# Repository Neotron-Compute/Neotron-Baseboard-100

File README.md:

# Neotron-Baseboard-100

The Neotron Baseboard 100 is an micro-ATX Neotron motherboard, with Neotron CPU Socket and 4x Neotron Expansion Slots.

You must fit a Neotron CPU card for this board to function (or attach a microcontroller dev-kit of your choice using jumper wires).

### Audio Codec

* Texas Instruments TLV320AIC23B
  * I²S + I²C interface
  * Amplified 32mW headphone output and line out
  * Microphone in and line in
  * TSSOP-28 package
* Triple 3.5mm TRS jack (Kycon STX-4335-5BGP-S1)
  * Headphone Out (green)
  * Line In (blue)
  * Microphone In (pink)
* AC'97 Pin Header
  * Headphone Out
  * Microphone In
* Extra line-level output pin header (e.g. for additional RCA audio jacks - operates in addition to 3.5mm headphone jack output)
* Internal line-level input pin header (e.g. for CD-ROM audio - disabled when line-in 3.5mm jack in-use)

### Super VGA output

* 15-pin D-Sub VGA interface
* 18-bit (6-6-6) RGB R2R DAC
* 3peak TPF133A or Texas Instruments THS7316 RGB video buffer
   * 36 MHz bandwidth - 1024x768@60Hz maximum
   * 6dB gain
   * Drives 75 ohm standard VGA interface
* I²C/DDC level shifter and EMC filter

### RS232 Interface

* Tx, Rx, RTS and CTS signals
* 3.3V TTL on the MCU side
* RS-232 signalling on a 9-pin D-Sub connector (or 10-pin IDC box header), wired DTE

### Board Management Controller

* ST Micro STM32F0 (STM32F030F4P6) microcontroller
  * 32-bit Arm Cortex-M0+ Core
  * 3.3V I/O
  * 8 KiB Flash
  * 4 KiB SRAM
  * TSSOP-20 package
* Controls two PS/2 ports
* Monitors 5V and 3.3V rails
* Controls system reset, soft-on and soft-off for main CPU
* Can the main 5V regulator on and off
* Runs from 3.3V stand-by regulator
* I²C interface (with dedicated IRQ line) with main CPU

| Pin | Name  | Peripheral | Function           |
|:----|:------|:-----------|:-------------------|
| 16  | VDD   | N/A        | 3.3V Digital Power |
| 5   | VDDA  | N/A        | 3.3V Analog Power  |
| 15  | VSS   | N/A        | Ground             |
| 1   | BOOT0 | BOOT0      | Boot Mode Select   |
| 4   | NRST  | Reset      | Reset BMC          |
| 6   | PA0   | ADC0       | Monitor 3.3V rail  |
| 7   | PA1   | ADC0       | Monitor 5V rail    |
| 8   | PA2   | USART1_TX  | Debug Log          |
| 9   | PA3   | Output     | Status LED         |
| 10  | PA4   | Output     | DC-DC Enable       |
| 11  | PA5   | Output     | System Reset       |
| 12  | PA6   | Input      | Reset Switch In    |
| 13  | PA7   | Input      | Power Switch In    |
| 17  | PA9   | I2C0_SCL   | Host comms         |
| 18  | PA10  | I2C0_SDA   | Host comms         |
| 19  | PA13  | IO         | PS/2 Data 1        |
| 20  | PA14  | IO         | PS/2 Clock 1       |
| 14  | PB1   | Output     | Host IRQ           |
| 2   | PF0   | IO         | PS/2 Data 0        |
| 3   | PF1   | IO         | PS/2 Clock 0       |

### PS/2 Keyboard and Mouse

* Twin mini 6-pin DIN ports
* Controlled via Board Management Controller

### Power Supply

* Unregulated 12V (8V to 28V) input fused with a PTC at 2A
* 3A 5.0V main regulator (DC-DC switch-mode regulator module)
* 30mA 3.3V stand-by regulator (a micropower linear regulator)
* 1A 3.3V regulator (a high-power 1117 type linear regulator)
* Controlled by the Board Management Controller

### CPU Socket

The CPU can either be designed to solder direct to your particular motherboard design, or it can be fitted to a second PCB 'CPU card' which plugs into a socket on the motherboard. We have designed a special 80-pin socket pinout, which provides all the signals for required for the standard peripherals available in this design.

The socket is basically two 2x20 pin headers, placed 130 mil apart. This should give enough space to fit even a TQFP-176 microcontroller and some TSOP-54 SDRAM.

The pins are labelled in row.column fashion, i.e. 1.1 is top left, 1.20 is top right and 4.20 is bottom right.

```
 +----- Pin 1.1
 |
 v
+---------------------------------------+
|o o o o o o o o o o o o o o o o o o o o|
|o o o o o o o o o o o o o o o o o o o o|
+---------------------------------------+

+---------------------------------------+
|o o o o o o o o o o o o o o o o o o o o|
|o o o o o o o o o o o o o o o o o o o o|
+---------------------------------------+
                                       ^
                                       |
                         Pin 4.20 -----+
```

| Pin  | Function             |
|:-----|:---------------------|
| 1.1  | VGA_RED5             |
| 1.2  | VGA_RED4             |
| 1.3  | VGA_RED3             |
| 1.4  | VGA_RED2             |
| 1.5  | VGA_RED1             |
| 1.6  | VGA_RED0             |
| 1.7  | VGA_GREEN5           |
| 1.8  | VGA_GREEN4           |
| 1.9  | VGA_GREEN3           |
| 1.10 | VGA_GREEN2           |
| 1.11 | VGA_GREEN1           |
| 1.12 | VGA_GREEN0           |
| 1.13 | VGA_BLUE5            |
| 1.14 | VGA_BLUE4            |
| 1.15 | VGA_BLUE3            |
| 1.16 | VGA_BLUE2            |
| 1.17 | VGA_BLUE1            |
| 1.18 | VGA_BLUE0            |
| 1.19 | VGA_HSYNC            |
| 1.20 | VGA_VSYNC            |
| 2.1  | VGA_DDC_SDA          |
| 2.2  | VGA_DDC_SCL          |
| 2.3  | UART_RX              |
| 2.4  | UART_TX              |
| 2.7  | 3V3                  |
| 2.8  | 3V3                  |
| 2.9  | 3V3                  |
| 2.10 | GND                  |
| 2.11 | GND                  |
| 2.12 | GND                  |
| 2.13 | AUDIO_BCLK_TO_CODEC  |
| 2.14 | AUDIO_DAT_TO_CODEC   |
| 2.15 | AUDIO_LR_TO_CODEC    |
| 2.16 | AUDIO_DAT_FROM_CODEC |
| 2.17 | AUDIO_LR_FROM_CODEC  |
| 2.18 | USB_EN               |
| 2.19 | USB_D-               |
| 2.20 | USB_D+               |
| 3.1  | I2C_SDA              |
| 3.2  | I2C_SCL              |
| 3.3  | UART_CTS             |
| 3.4  | UART_RTS             |
| 3.7  | GND                  |
| 3.8  | GND                  |
| 3.9  | GND                  |
| 3.10 | 5V                   |
| 3.11 | 5V                   |
| 3.12 | 5V                   |
| 3.13 | ~SPI_CS7             |
| 3.14 | ~SPI_CS6             |
| 3.15 | ~SPI_CS5             |
| 3.16 | ~SPI_CS4             |
| 3.17 | ~SPI_CS3             |
| 3.18 | ~SPI_CS2             |
| 3.19 | ~SPI_CS1             |
| 3.20 | ~SPI_CS0             |
| 4.1  | ~SDMMC_CARD_DETECT   |
| 4.2  | ~SDMMC_WRITE_PROT    |
| 4.3  | SDMMC_DAT2           |
| 4.4  | SDMMC_DAT3           |
| 4.5  | SDMMC_CMD            |
| 4.6  | SDMMC_CLK            |
| 4.7  | SDMMC_DAT0           |
| 4.8  | SDMMC_DAT1           |
| 4.9  | SPI_COPI             |
| 4.10 | SPI_CIPO             |
| 4.11 | SPI_CLK              |
| 4.12 | ~RESET               |
| 4.13 | ~IRQ7                |
| 4.14 | ~IRQ6                |
| 4.15 | ~IRQ5                |
| 4.16 | ~IRQ4                |
| 4.17 | ~IRQ3                |
| 4.18 | ~IRQ2                |
| 4.19 | ~IRQ1                |
| 4.20 | ~IRQ0                |

## Expansion

The (up-to) seven expansion sockets allow you to add on I²C or SPI based devices at a later date. Each provides a single chip-select and a single IRQ line - the motherboard design should ensure each socket gets a unique signal for each of these. Each expansion device should also contain a AT24C256 or similar EEPROM device. To allow these EEPROM devices to be scanned, each slot also contains three `EEPROM_ADDRESS` pins, tied to Vcc or GND in a unique combination. These should be connected through to the EEPROM address lines on your AT24C256, thus ensuring that each expansion card has its EEPROM at a unique address - 0x50 on Slot 0 through to a maximum possible 0x57 for Slot 7. Where your board has on-board devices, you should fit an AT24C256 EEPROM for each device so that the on-board devices can be discovered, exactly as if they were on an expansion card.

The expansion slot is a simple 2x10 header. We suggest the use of a TE card-edge connector, but you could equally use two 1x10 pin-headers if desired.

The pin functions are:

```
     SPI_COPI   1    2   GND
     SPI_CIPO   3    4   GND
      SPI_CLK   5    6   GND
      ~SPI_CS   7    8   ~IRQ
      I2C_SDA   9   10   I2C_SCL
 EEPROM_ADDR0   11  12   EEPROM_ADDR1
 EEPROM_ADDR2   13  14   ~RESET
           5V   15  16   5V
          3V3   17  18   3V3
          GND   19  20   GND
```

## Expansion Ideas

Why not design and build your own expansion card? You could try designing:

* A dual Atari/SEGA 9-pin Joypad Interface
* An Ethernet card, e.g. with an ENC28J60 SPI/Ethernet interface IC
* A Mikro Eletronika Click adaptor, allow many of the range of [Click board](https://www.mikroe.com/click) to be fitted
* A Wi-Fi/Bluetooth card, using an Espressif ESP32
* A second processor card - perhaps with a RISC-V microcontroller, or classic Zilog Z80
* An OPL2 or OPL3 based FM synthesiser card
* An ISA adaptor card (taking an ISA card at right-angles, i.e. parallel to the base board) - a simple microcontroller should be able to bit-bang the ISA bus at 8 MHz and offer an SPI peripheral interface to the Neotron Expansion Slot
* An IDE interface card, allowing 40-pin IDE Hard Disk Drives and CD-ROM drives to be used - this will be quite similar to an ISA bus adaptor
* A floppy drive controller card - either using an eSPI Super I/O chip, or connecting a legacy ISA bus floppy controller as per the ISA adaptor
* A video card for a second monitor output, perhaps based on the CPLD used in the [VGAtonic](https://hackaday.io/project/6309-vga-graphics-over-spi-and-serial-vgatonic)

## Changelog

See [CHANGELOG.md](./CHANGELOG.md) for a list of detailed changes.

## Licence

This schematic and PCB design is Copyright (c) The Neotron Developers.

This work is licensed under a [Creative Commons Attribution-ShareAlike 4.0 International License](http://creativecommons.org/licenses/by-sa/4.0/).

## Contribution Agreement

Unless you explicitly state otherwise, any contribution intentionally submitted for inclusion in the work by you, as defined in the Apache-2.0 license, shall be licensed as above, without any additional terms or conditions.

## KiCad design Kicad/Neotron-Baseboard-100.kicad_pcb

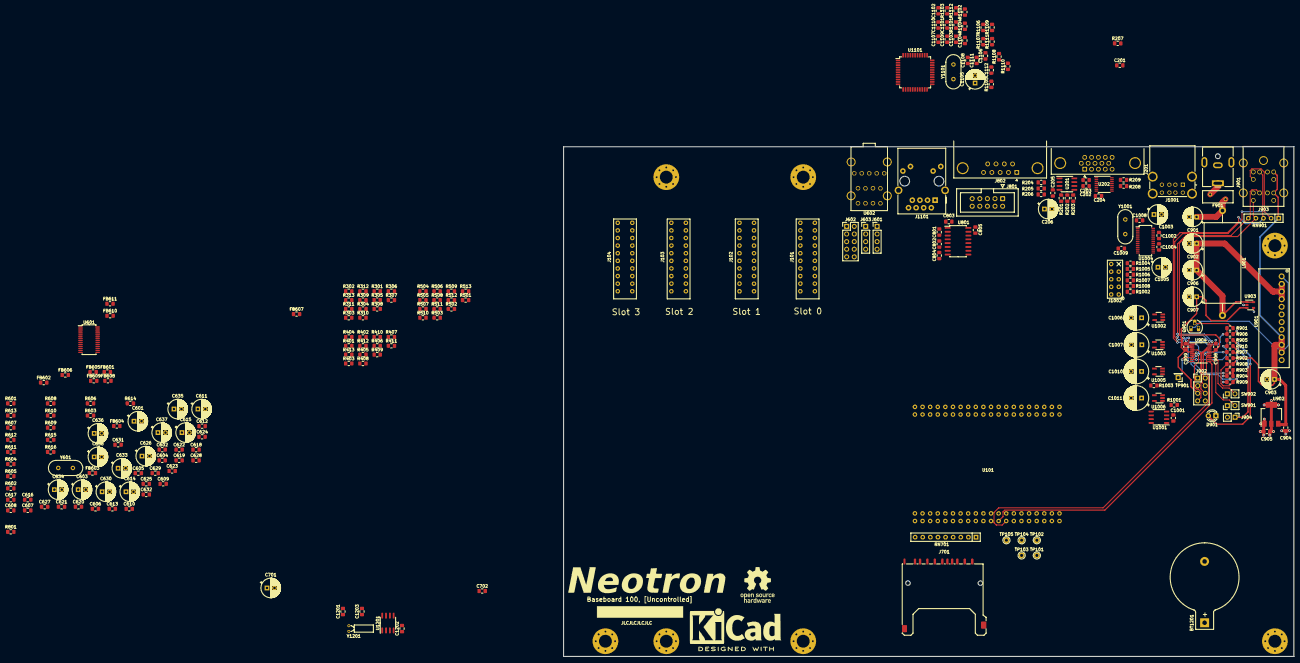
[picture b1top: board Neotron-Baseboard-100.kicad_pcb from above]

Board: 4 copper layers, 243.8 x 170.2 mm, 257 parts (0 on the bottom side), 218 nets.

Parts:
BT1201: Coin Cell; BatteryHolder_Keystone_103_1x20mm
C201: 220n; C_0805_2012Metric_Pad1.15x1.40mm_HandSolder
C202, C203, C204, C205, C602, C604, C612, C613, C627, C702, C801, C802, C803, C804, C805, C904, C908, C909, C1001, C1002, C1004, C1106, C1107, C1108, C1109, C1110, C1201: 100n; C_0805_2012Metric_Pad1.15x1.40mm_HandSolder
C206, C601, C603, C611, C626, C633, C634, C635, C636, C637, C638, C701: 10u; CP_Radial_D6.3mm_P2.50mm
C605, C606, C620, C621: 470n; C_0805_2012Metric_Pad1.15x1.40mm_HandSolder
C607, C608, C609, C610, C616, C617, C618, C619, C622, C623, C624, C625, C632: DNF; C_0805_2012Metric_Pad1.15x1.40mm_HandSolder
C614, C615: 220u; CP_Radial_D6.3mm_P2.50mm
C628, C629: 22p; C_0805_2012Metric_Pad1.15x1.40mm_HandSolder
C630: 1u; CP_Radial_D6.3mm_P2.50mm
C631: 47p; C_0805_2012Metric_Pad1.15x1.40mm_HandSolder
C901, C902: 100u 50V; CP_Radial_D6.3mm_P2.50mm
C903: 22u; CP_Radial_D6.3mm_P2.50mm
C905: 1u; C_0805_2012Metric_Pad1.15x1.40mm_HandSolder
C906: 1u 50V; CP_Radial_D6.3mm_P2.50mm
C907, C1003, C1005: 4u7; CP_Radial_D6.3mm_P2.50mm
C1006, C1007, C1010, C1011: 120u; CP_Radial_D8.0mm_P3.50mm
C1008, C1009, C1103, C1104: 12p; C_0805_2012Metric_Pad1.15x1.40mm_HandSolder
C1101, C1102: 10n; C_0805_2012Metric_Pad1.15x1.40mm_HandSolder
C1105: 10u Low ESR; CP_Radial_D6.3mm_P2.50mm
C1111, C1112: 1n; C_0805_2012Metric_Pad1.15x1.40mm_HandSolder
C1202, C1203: 6p; C_0805_2012Metric_Pad1.15x1.40mm_HandSolder
D901: LED; LED_D3.0mm
F901: 32V 2A PTC; Fuse_BelFuse_0ZRE0016FF_L9.9mm_W3.8mm
FB601, FB602, FB603, FB604, FB605, FB606, FB608, FB609, FB610, FB611: 220R@100MHz; L_0805_2012Metric_Pad1.15x1.40mm_HandSolder
FB607: 600R@100MHz; L_0805_2012Metric_Pad1.15x1.40mm_HandSolder
H101, H102, H103, H104, H105, H106, H107: MountingHole_Pad; MountingHole_4.3mm_M4_Pad_Via
J101, J102, J103, J104: Neotron-Expansion-Slot
J201: DE15HD; DSUB-15-HD_Female_Horizontal_P2.29x1.98mm_EdgePinOffset3.03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
J601: Line Out; PinHeader_1x04_P2.54mm_Vertical
J602: AC'97 Audio Header; PinHeader_2x05_P2.54mm_Vertical
J603: CD Audio In; PinHeader_1x04_P2.54mm_Vertical
J701: SD_Card; SD_Kyocera_145638009211859+
J801: Conn_02x05; IDC-Header_2x05_P2.54mm_Vertical
J802: DB9_Male_MountingHoles; DSUB-9_Male_Horizontal_P2.77x2.84mm_EdgePinOffset7.70mm_Hou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
J901: Jack-DC; BarrelJack_CUI_PJ-063AH_Horizontal
J902: Conn_02x04_Odd_Even; PinHeader_2x04_P2.54mm_Vertical
J903: Double-mini-DIN-6; Double_mini-DIN_6
J904: Header; PinHeader_1x02_P2.54mm_Vertical
J1001: USB Ports External; CUI_UJ2-ADH-1-TH
J1002: USB Ports Internal; USB_Header
J1101: RJ45 MagJack; RJ45_Amphenol_RJMG1BD3B8K1ANR
L901: 22uH 6A; L_Axial_L26.7mm_D12.1mm_P35.00mm_Horizontal_Vishay_IHA-103
LOGO101: Neotron Logo; logo
LOGO102: Kicad Logo; KiCad-Logo2_12mm_SilkScreen
LOGO103: OSHW Logo; OSHW-Logo_11.4x12mm_SilkScreen
Q901: BC548; TO-92_HandSolder
R201, R202, R203: 75; R_0805_2012Metric_Pad1.15x1.40mm_HandSolder
R204, R205, R206, R613, R902, R903, R904, R906, R907, R908, R909, R1001, R1003, R1004, R1005, R1006, R1007, R1008: 10k; R_0805_2012Metric_Pad1.15x1.40mm_HandSolder
R207, R801, R1110: DNF; R_0805_2012Metric_Pad1.15x1.40mm_HandSolder
R208, R209: 1k5; R_0805_2012Metric_Pad1.15x1.40mm_HandSolder
R301, R302, R303, R304, R305, R306, R312, R401, R402, R403, R404, R405, R406, R412, R501, R502, R503, R504, R505, R506, R512: 24k 0.5%; R_0805_2012Metric_Pad1.15x1.40mm_HandSolder
R307, R308, R309, R310, R311, R407, R408, R409, R410, R411, R507, R508, R509, R510, R511: 12k 0.5%; R_0805_2012Metric_Pad1.15x1.40mm_HandSolder
R313, R413, R513: 3300; R_0805_2012Metric_Pad1.15x1.40mm_HandSolder
R601, R602: 100; R_0805_2012Metric_Pad1.15x1.40mm_HandSolder
R603, R604, R605, R606: 47k; R_0805_2012Metric_Pad1.15x1.40mm_HandSolder
R607, R608, R609, R610, R612: 4k7; R_0805_2012Metric_Pad1.15x1.40mm_HandSolder
R611: 2k2; R_0805_2012Metric_Pad1.15x1.40mm_HandSolder
R614, R615, R616: 2R2; R_0805_2012Metric_Pad1.15x1.40mm_HandSolder
R901: 2k; R_0805_2012Metric_Pad1.15x1.40mm_HandSolder
R905, R910: 1k; R_0805_2012Metric_Pad1.15x1.40mm_HandSolder
R1002: 2k7 1%; R_0805_2012Metric_Pad1.15x1.40mm_HandSolder
R1101, R1103, R1104, R1107: 49R9 1%; R_0805_2012Metric_Pad1.15x1.40mm_HandSolder
R1102, R1106: 10; R_0805_2012Metric_Pad1.15x1.40mm_HandSolder
R1105: 100k; R_0805_2012Metric_Pad1.15x1.40mm_HandSolder
R1108, R1109: 180; R_0805_2012Metric_Pad1.15x1.40mm_HandSolder
R1111: 1M; R_0805_2012Metric_Pad1.15x1.40mm_HandSolder
R1112: 12k4 1%; R_0805_2012Metric_Pad1.15x1.40mm_HandSolder
RN701: 8x10k; R_Array_SIP9
RN901: 2k7 x 4; R_Array_SIP5
SW901, SW902: SW_DIP_x01; PinHeader_1x02_P2.54mm_Vertical
TP101, TP102, TP103, TP104, TP105: TestPoint; TestPoint_THTPad_D2.0mm_Drill1.0mm
TP901: TestPoint; PinHeader_1x01_P2.54mm_Vertical
U101: Neotron-CPU; Neotron_CPU_Socket
U201: THS7316; SOIC-8_3.9x4.9mm_P1.27mm
U202: TPD7S019; SSOP-16_3.9x4.9mm_P0.635mm
U601: TLV320AIC23BPW; TSSOP-28_4.4x9.7mm_P0.65mm
U602: STX-4335-5BGP-S1
U801: ST3232CDR; SO-16_5.3x10.2mm_P1.27mm
U901: 5V DC-DC Module; K78xx-3AR3
U902: TLV1117 3.3V 1A; SOT-223-3_TabPin2
U903: MAX1615; SOT-23-5
U904: STM32F030F4Px; TSSOP-20_4.4x6.5mm_P0.65mm
U1001: AP2501; SO-8_3.9x4.9mm_P1.27mm
U1002, U1003, U1005, U1006: MIC2005A-2YM5; SOT-23-5_HandSoldering
U1004: XR22404CG28; SSOP-28_3.9x9.9mm_P0.635mm
U1101: ENC424J600; TQFP-44_10x10mm_P0.8mm
U1201: MCP7940; SOIC-8_3.9x4.9mm_P1.27mm
Y601, Y1001: 12M; Crystal_HC49-4H_Vertical
Y1101: 25M; Crystal_HC49-4H_Vertical
Y1201: 32,768 Hz; Crystal_DS26_D2.0mm_L6.0mm_Horizontal

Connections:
+3.3VP: C907.1, C908.1, C909.1, J902.5, U903.3, U904.5, U904.16
+3V3: C204.2, C205.2, C206.2, C701.1, C702.1, C805.2, C905.1, C1106.1, C1107.1, C1108.1, C1109.1, C1110.1, C1111.1, C1112.1, C1201.1, FB608.2, FB610.2, J101.17, J101.18, J102.11, J102.17, J102.18, J103.12, J103.17, J103.18, J104.11, J104.12, J104.17, J104.18, J701.4, R908.1, R1001.1, R1003.1, R1101.2, R1102.1, R1103.1, R1104.2, R1105.1, R1106.1, R1107.1, RN701.1, U101.2.7, U101.2.8, U101.2.9, U201.4, U202.7, U801.16, U902.2, U1101.4, U1101.12, U1101.15, U1101.18, U1101.44, U1201.8
+5V: C202.2, C203.2, C903.1, C904.1, C1001.1, FB609.2, J101.15, J101.16, J102.15, J102.16, J103.15, J103.16, J104.15, J104.16, J201.9, J903.4, J903.10, R208.1, R209.1, R902.1, RN901.1, U101.3.10, U101.3.11, U101.3.12, U202.1, U202.2, U901.4, U902.3, U1001.2, U1001.3
+BATT: BT1201.1, U1201.3
/Audio/3V3_ANALOG: C601.1, C602.1, C603.1, C604.1, C634.1, R614.1, U601.8, U601.14
/Audio/3V3_DIGITAL: C611.1, C612.1, C613.1, C638.1, R616.1, U601.1, U601.27
/Audio/5V0_ANALOG: C636.1, J602.7, R615.1
/Audio/AUDIO_BIT_CLK_TO_CODEC: U101.2.13, U601.3
/Audio/AUDIO_DAT_FROM_CODEC: U101.2.16, U601.6
/Audio/AUDIO_DAT_TO_CODEC: U101.2.14, U601.4
/Audio/AUDIO_LR_FROM_CODEC: U101.2.17, U601.7
/Audio/AUDIO_LR_TO_CODEC: U101.2.15, U601.5
/Audio/BIASOUT: R611.2, U601.17
/Audio/CDInL: J603.1, U602.34
/Audio/CDInR: J603.4, U602.33
/Audio/FrontHPL: C617.2, FB603.1, J602.9
/Audio/FrontHPR: C619.2, FB604.1, J602.5
/Audio/FrontMicL: J602.1, U602.4
/Audio/FrontMicR: J602.3, U602.3
/Audio/LineL: C608.2, FB601.1, J601.1
/Audio/LineR: C610.2, FB602.1, J601.4
/Audio/MICIN: R612.1, U601.18
/Audio/RearHPL: J602.10, U602.25
/Audio/RearHPR: J602.6, U602.22
/Audio/RearInL: C623.2, FB605.1, U602.35
/Audio/RearInR: C625.2, FB606.1, U602.32
/Audio/RearMicL: C632.2, FB607.1, R613.2, U602.2, U602.5
/B0: R501.1, U101.1.18
/B1: R502.1, U101.1.17
/B2: R503.1, U101.1.16
/B3: R504.1, U101.1.15
/B4: R505.1, U101.1.14
/B5: R506.1, U101.1.13
/G0: R401.1, U101.1.12
/G1: R402.1, U101.1.11
/G2: R403.1, U101.1.10
/G3: R404.1, U101.1.9
/G4: R405.1, U101.1.8
/G5: R406.1, U101.1.7
/I2C_SCL: J101.9, J102.9, J103.9, J104.9, J902.1, U101.3.2, U601.24, U1201.6
/I2C_SDA: J101.10, J102.10, J103.10, J104.10, J902.3, U101.3.1, U601.23, U1201.5
/Power Supply/BOOT0: J902.7, R907.1, U904.1
/Power Supply/DC_ON: R901.2, R906.1, U904.10
/Power Supply/MON_3V3: R908.2, R909.1, U904.6
/Power Supply/MON_5V: R903.2, R904.1, U904.7
/Power Supply/PS2_CLK0: J903.5, RN901.2, U904.3
/Power Supply/PS2_CLK1: J903.11, RN901.4, U904.20
/Power Supply/PS2_DAT0: J903.1, RN901.3, U904.2
/Power Supply/PS2_DAT1: J903.7, RN901.5, U904.19
/Power Supply/SCL_U1TX: J902.2, U904.17
/Power Supply/SDA_U1RX: J902.4, U904.18
/Power Supply/USART1_TX: TP901.1, U904.8
/Power Supply/~BMC_RST: J902.6, U904.4
/Power Supply/~BUTTON_PWR: SW902.2, U904.13
/Power Supply/~BUTTON_RST: SW901.2, U904.12
/Power Supply/~PSU_EN: Q901.1, U901.1
/Power Supply/~STATUS_LED: R905.1, R910.1, U904.9
/R0: R301.1, U101.1.6
/R1: R302.1, U101.1.5
/R2: R303.1, U101.1.4
/R3: R304.1, U101.1.3
/R4: R305.1, U101.1.2
/R5: R306.1, U101.1.1
/SD Card/CLK: J701.5, RN701.5, U101.4.5
/SD Card/CMD: J701.2, RN701.4, U101.4.6
/SD Card/DAT0: J701.7, RN701.6, U101.4.4
/SD Card/DAT1: J701.8, RN701.7, U101.4.3
/SD Card/DAT2: J701.9, RN701.2, U101.4.8
/SD Card/DAT3: J701.1, RN701.3, U101.4.7
/SD Card/~CARD_DETECT: J701.10, RN701.8, U101.4.1
/SD Card/~WRITE_PROTECT: J701.11, RN701.9, U101.4.2
/SPI_CIPO: J101.3, J102.3, J103.3, J104.3, U101.4.10, U1101.35
/SPI_CLK: J101.5, J102.5, J103.5, J104.5, U101.4.11, U1101.37
/SPI_COPI: J101.1, J102.1, J103.1, J104.1, U101.4.9, U1101.36
/Serial/RS232_CTS_IN: J801.8, J802.8, U801.8
/Serial/RS232_CTS_TO_MCU: U101.3.3, U801.9
/Serial/RS232_RTS_FROM_MCU: U101.3.4, U801.10
/Serial/RS232_RTS_OUT: J801.7, J802.7, U801.7
/Serial/RS232_RX_IN: J801.2, J802.2, U801.13
/Serial/RS232_RX_TO_MCU: U101.2.3, U801.12
/Serial/RS232_TX_FROM_MCU: U101.2.4, U801.11
/Serial/RS232_TX_OUT: J801.3, J802.3, U801.14
/USB/USBD1+: J1001.2, U1004.11
/USB/USBD1-: J1001.3, U1004.10
/USB/USBD2+: J1001.6, U1004.9
/USB/USBD2-: J1001.7, U1004.8
/USB/USBD3+: J1002.2, U1004.7
/USB/USBD3-: J1002.3, U1004.6
/USB/USBD4+: J1002.6, U1004.5
/USB/USBD4-: J1002.7, U1004.4
/USB/USBD+: U101.2.20, U1004.16
/USB/USBD-: U101.2.19, U1004.15
/USB/USB_3V3: C1002.1, C1003.1, R1004.1, R1005.1, R1006.1, R1007.1, U1004.21
/USB/USB_5V: C1004.1, C1005.1, U1001.6, U1001.7, U1002.1, U1003.1, U1004.20, U1005.1, U1006.1
/USB/~ENABLE: R1001.2, U101.2.18, U1001.4
/Video/BLUE_ANA: R206.2, R506.2, R511.1, R513.1, U201.3
/Video/DDC_SCL: U101.2.2, U202.11
/Video/DDC_SDA: U101.2.1, U202.10
/Video/GREEN_ANA: R205.2, R406.2, R411.1, R413.1, U201.2
/Video/HSYNC: U101.1.19, U202.15
/Video/RED_ANA: R204.2, R306.2, R311.1, R313.1, U201.1
/Video/VGA_BLU: J201.3, R203.1, U202.5
/Video/VGA_DDC_SCL: J201.15, R209.2, U202.12
/Video/VGA_DDC_SDA: J201.12, R208.2, U202.9
/Video/VGA_GRN: J201.2, R202.1, U202.4
/Video/VGA_HSYNC: J201.13, U202.16
/Video/VGA_RED: J201.1, R201.1, U202.3
/Video/VGA_VSYNC: J201.14, U202.14
/Video/VSYNC: U101.1.20, U202.13
/~CS0: J101.7, U101.3.20
/~CS1: J102.7, U101.3.19
/~CS2: J103.7, U101.3.18
/~CS3: J104.7, U101.3.17
/~CS4: U101.3.16, U1101.34
/~CS5: TP102.1, U101.3.15
/~CS6: TP104.1, U101.3.14
/~CS7: TP105.1, U101.3.13
/~IRQ0: J101.8, U101.4.20
/~IRQ1: J102.8, U101.4.19
/~IRQ2: J103.8, U101.4.18
/~IRQ3: J104.8, U101.4.17
/~IRQ4: R1105.2, U101.4.16, U1101.24
/~IRQ5: TP101.1, U101.4.15
/~IRQ6: TP103.1, U101.4.14
/~IRQ7: U101.4.13, U904.14
/~RESET: J101.14, J102.14, J103.14, J104.14, U101.4.12, U904.11
GND: BT1201.2, C201.1, C202.1, C203.1, C204.1, C205.1, C206.1, C611.2, C612.2, C613.2, C628.1, C629.2, C633.2, C634.2, C635.2, C636.2, C701.2, C702.2, C803.1, C804.1, C805.1, C901.2, C902.2, C903.2, C904.2, C905.2, C906.2, C907.2, C908.2, C909.2, C1001.2, C1002.2, C1003.2, C1004.2, C1005.2, C1006.2, C1007.2, C1008.2, C1009.2, C1010.2, C1011.2, C1101.2, C1102.2, C1103.2, C1104.2, C1105.2, C1106.2, C1107.2, C1108.2, C1109.2, C1110.2, C1111.2, C1112.2, C1201.2, C1202.2, C1203.2, D901.1, FB611.1, H101.1, H102.1, H103.1, H104.1, H105.1, H106.1, H107.1, J101.2, J101.4, J101.6, J101.11, J101.12, J101.13, J101.19, J101.20, J102.2, J102.4, J102.6, J102.12, J102.13, J102.19, J102.20, J103.2, J103.4, J103.6, J103.11, J103.13, J103.19, J103.20, J104.2, J104.4, J104.6, J104.13, J104.19, J104.20, J201.5, J201.6, J201.7, J201.8, J201.10, J701.3, J701.6, J701.12, J701.13, J801.5, J802.5, J901.2, J902.8, J903.3, J903.9, J904.2, J1001.4, J1001.8, J1001.9, J1002.4, J1002.8, J1002.9, J1101.L2, J1101.L3, J1101.R8, Q901.3, R204.1, R205.1, R206.1, R207.1, R312.2, R313.2, R412.2, R413.2, R512.2, R513.2, R801.2, R904.2, R906.2, R907.2, R909.2, R1002.2, R1008.2, R1110.2, R1112.2, SW901.1, SW902.1, U101.2.10, U101.2.11, U101.2.12, U101.3.7, U101.3.8, U101.3.9, U201.5, U202.6, U601.22, U601.28, U801.15, U901.3, U902.1, U903.2, U903.4, U904.15, U1001.1, U1002.2, U1003.2, U1004.1, U1005.2, U1006.2, U1101.1, U1101.13, U1101.14, U1101.19, U1101.22, U1101.33, U1101.42, U1201.4
GNDA: C601.2, C602.2, C603.2, C604.2, C607.1, C608.1, C609.1, C610.1, C616.1, C617.1, C618.1, C619.1, C622.1, C623.1, C624.1, C625.1, C626.2, C627.2, C631.1, C632.1, C637.2, C638.2, FB611.2, J601.2, J601.3, J602.2, J602.4, J603.2, J603.3, R603.2, R604.1, R605.2, R606.1, R609.2, R610.1, R613.1, U601.11, U601.15, U602.1
unnamed: C201.2, U202.8
unnamed: C605.1, U601.12
unnamed: C605.2, R601.2
unnamed: C606.1, U601.13
unnamed: C606.2, R602.2
unnamed: C607.2, FB601.2, R601.1, R604.2
unnamed: C609.2, FB602.2, R602.1, R603.1
unnamed: C614.1, U601.9
unnamed: C614.2, C616.2, FB603.2, R606.2
unnamed: C615.1, U601.10
unnamed: C615.2, C618.2, FB604.2, R605.1
unnamed: C620.1, U601.20
unnamed: C620.2, R607.2, R610.2
unnamed: C621.1, U601.19
unnamed: C621.2, R608.2, R609.1
unnamed: C622.2, FB605.2, R607.1
unnamed: C624.2, FB606.2, R608.1
unnamed: C626.1, C627.1, U601.16
unnamed: C628.2, U601.25, Y601.1
unnamed: C629.1, U601.26, Y601.2
unnamed: C630.1, R612.2
unnamed: C630.2, C631.2, FB607.2, R611.1
unnamed: C633.1, FB608.1, R614.2
unnamed: C635.1, FB609.1, R615.2
unnamed: C637.1, FB610.1, R616.2
unnamed: C801.1, U801.3
unnamed: C801.2, U801.1
unnamed: C802.1, U801.4
unnamed: C802.2, U801.5
unnamed: C803.2, U801.2
unnamed: C804.2, U801.6
unnamed: C901.1, F901.1, L901.1
unnamed: C902.1, C906.1, L901.2, U901.2, U903.1, U903.5
unnamed: C1006.1, J1001.1, U1002.5
unnamed: C1007.1, J1001.5, U1003.5
unnamed: C1008.1, U1004.2, Y1001.2
unnamed: C1009.1, U1004.3, Y1001.1
unnamed: C1010.1, J1002.1, U1005.5
unnamed: C1011.1, J1002.5, U1006.5
unnamed: C1101.1, J1101.R4, R1102.2
unnamed: C1102.1, J1101.R5, R1106.2
unnamed: C1103.1, R1111.2, Y1101.1
unnamed: C1104.1, U1101.3, Y1101.2
unnamed: C1105.1, U1101.43
unnamed: C1202.1, U1201.2, Y1201.2
unnamed: C1203.1, U1201.1, Y1201.1
unnamed: D901.2, R905.2
unnamed: F901.2, J901.1
unnamed: J201.0, R207.2
unnamed: J802.0, R801.1
unnamed: J904.1, R910.2
unnamed: J1101.13, R1110.1
unnamed: J1101.L1, R1109.2
unnamed: J1101.L4, R1108.2
unnamed: J1101.R1, R1101.1, U1101.20
unnamed: J1101.R2, R1103.2, U1101.21
unnamed: J1101.R3, R1104.1, U1101.16
unnamed: J1101.R6, R1107.2, U1101.17
unnamed: Q901.2, R901.1
unnamed: R201.2, U201.8
unnamed: R202.2, U201.7
unnamed: R203.2, U201.6
unnamed: R301.2, R307.2, R312.1
unnamed: R302.2, R307.1, R308.2
unnamed: R303.2, R308.1, R309.2
unnamed: R304.2, R309.1, R310.2
unnamed: R305.2, R310.1, R311.2
unnamed: R401.2, R407.2, R412.1
unnamed: R402.2, R407.1, R408.2
unnamed: R403.2, R408.1, R409.2
unnamed: R404.2, R409.1, R410.2
unnamed: R405.2, R410.1, R411.2
unnamed: R501.2, R507.2, R512.1
unnamed: R502.2, R507.1, R508.2
unnamed: R503.2, R508.1, R509.2
unnamed: R504.2, R509.1, R510.2
unnamed: R505.2, R510.1, R511.2
unnamed: R902.2, R903.1
unnamed: R1002.1, U1004.14
unnamed: R1003.2, U1002.4, U1003.4, U1004.26, U1005.4, U1006.4
unnamed: R1004.2, U1004.17
unnamed: R1005.2, U1004.19
unnamed: R1006.2, U1004.18
unnamed: R1007.2, U1004.27
unnamed: R1008.1, U1004.22
unnamed: R1108.1, U1101.10
unnamed: R1109.1, U1101.9
unnamed: R1111.1, U1101.2
unnamed: R1112.1, U1101.11
unnamed: U1002.3, U1003.3, U1004.25, U1005.3, U1006.3

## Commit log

2021-01-01 Bring in Neotron Common at 0.2.0
2021-01-01 Adding README.
2021-01-01 Create skeleton Kicad file.
2021-01-01 Imported top-level schematic from common.
2021-01-01 Bring over basic PCB shape.
    Dropped down to "short micro-ATX" - 9.6" across, 6.7" high.
2021-01-01 Wiring up top sheet.
2021-01-01 Updated to Common v0.3.0.
2021-01-01 Updated common to 0.4.0 and added some part numbers.
2021-01-02 Working on PSU layout.
2021-01-03 Working on laying out USB hub.
2021-01-03 Wired up UART and expansion slots.
2021-01-07 Updating to common 0.5.0
2021-01-08 Added I2C addresses.
2021-01-08 Updated to v0.6.0
    Started re-laying out PSU
2021-01-16 Update README - copying over from Common
2021-01-16 Removed USB and Ethernet from README

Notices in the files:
Kicad/Neotron-Baseboard-100.kicad_pcb:
Licensed as CC BY-SA
Copyright (c) The Neotron Developers, 2021
